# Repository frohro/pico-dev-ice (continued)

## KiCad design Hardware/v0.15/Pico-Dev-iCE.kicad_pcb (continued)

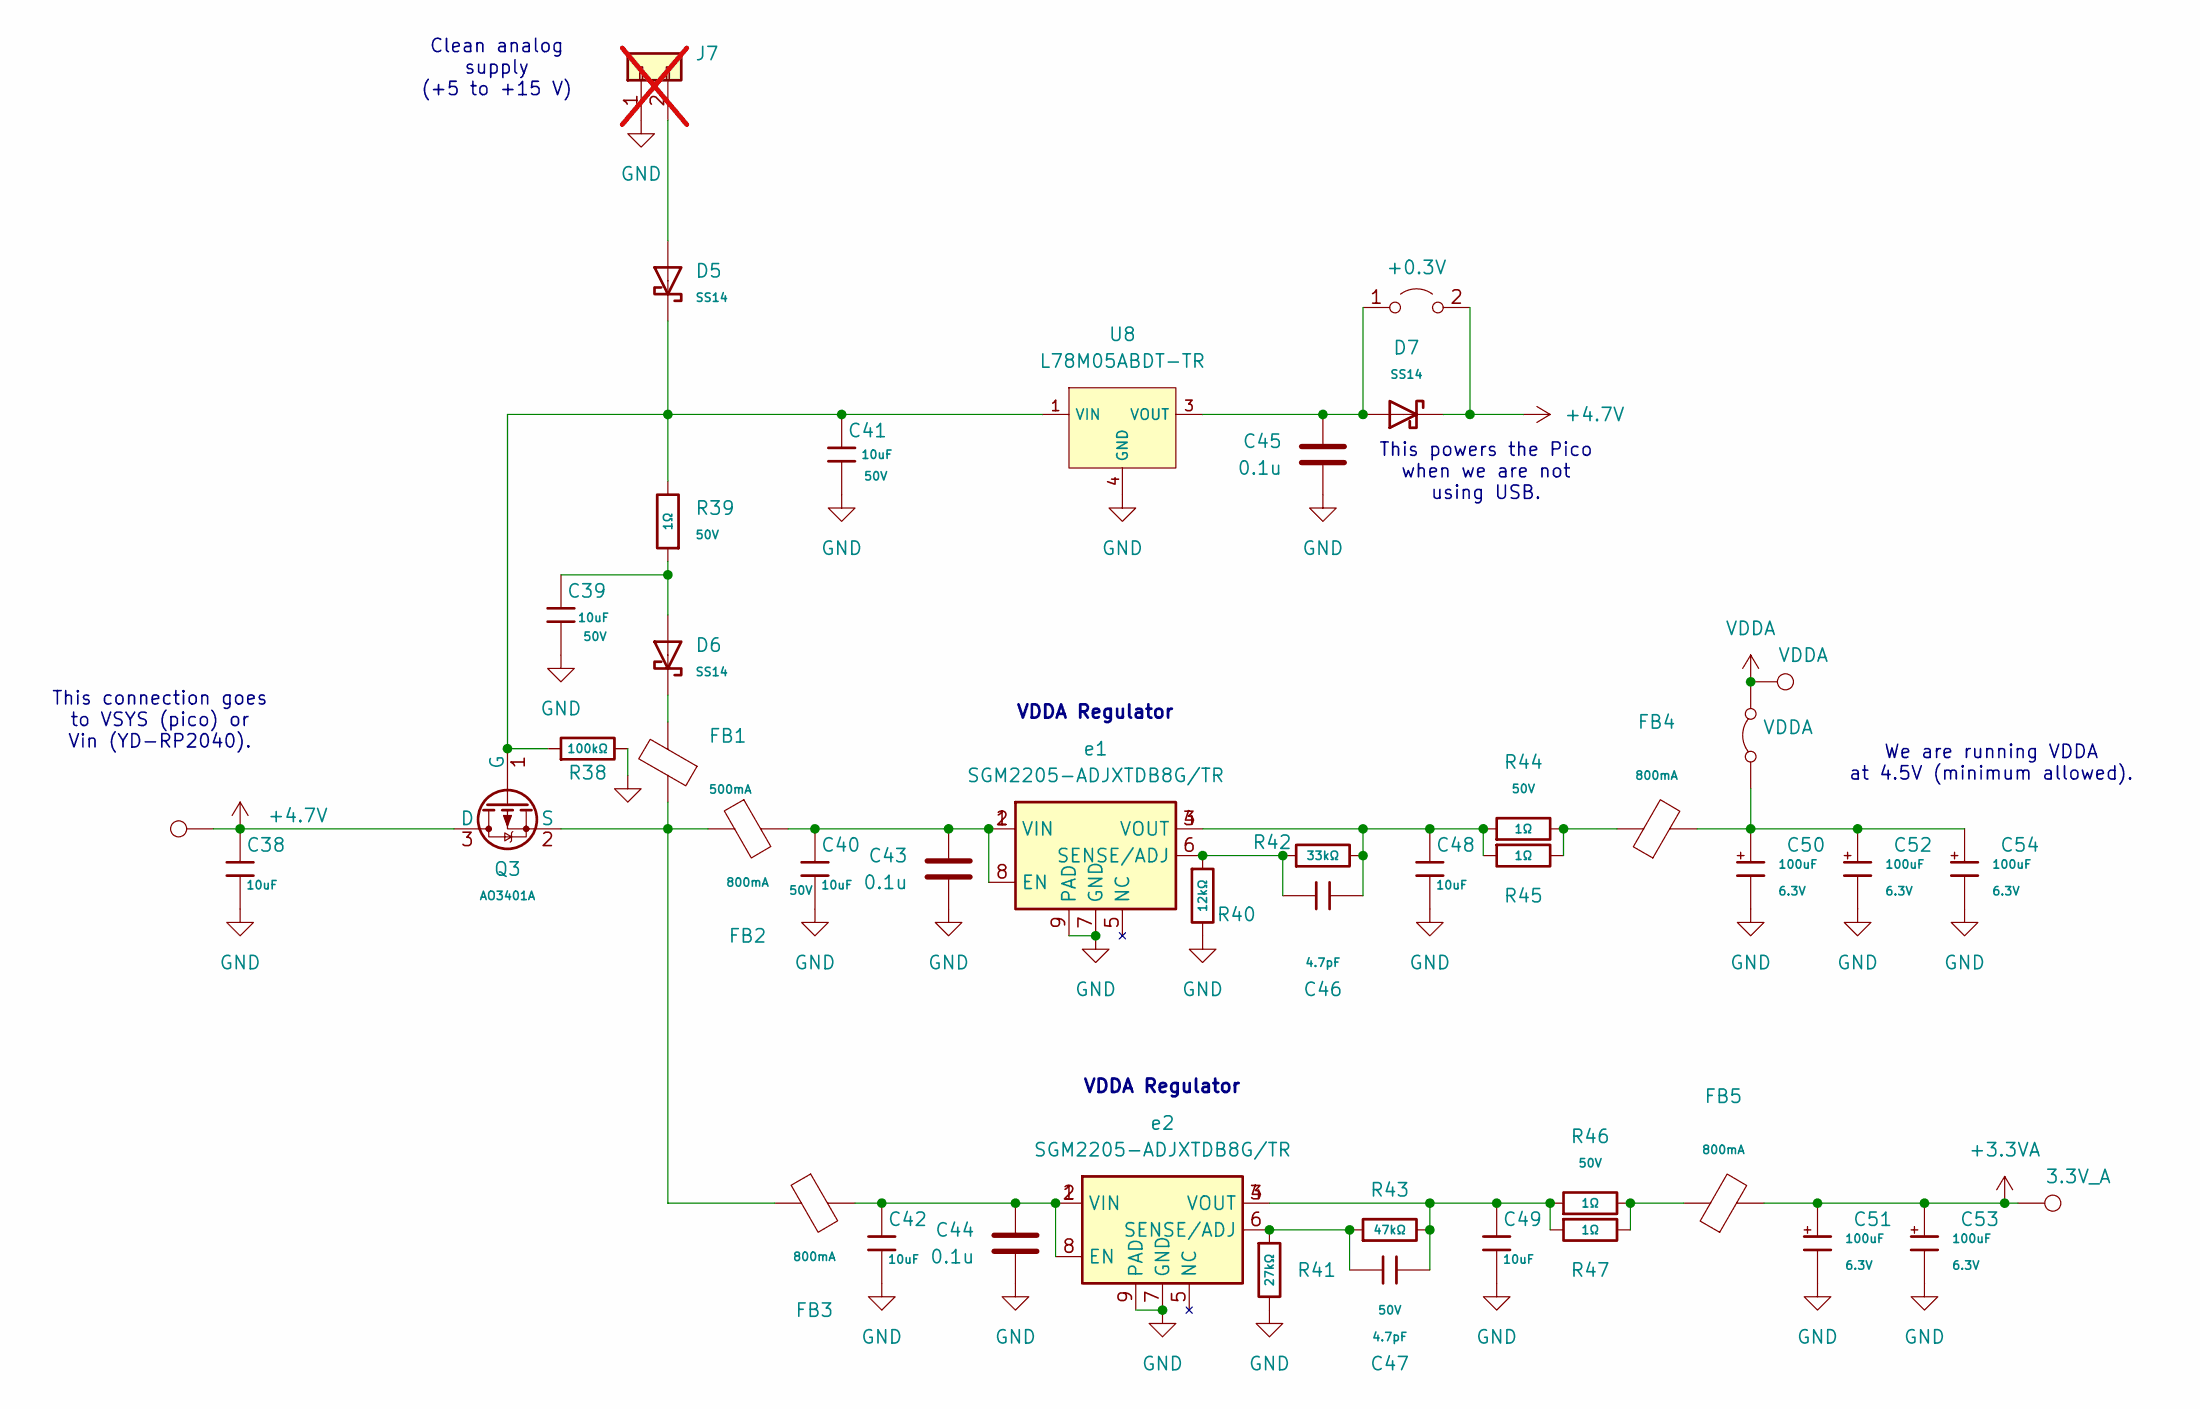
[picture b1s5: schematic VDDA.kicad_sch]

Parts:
C38, C39, C40, C41, C42, C48, C49: 10uF; C_0805; Voltage Rated 50V; Tolerance ±10%; Part GRM21BR61H106KE43L; LCSC C440198
C43, C44, C45: 0.1u; C_0805_2012Metric; LCSC C49678
C46, C47: 4.7pF; C_0603; Voltage Rated 50V; Part 0603CG4R7C500NT; LCSC C1669
C50, C51, C52, C53, C54: 100uF; C_CASE-B-3528-21(mm); Tolerance ±10%; Rated Voltage 6.3V; Part TAJB107K006RNJ; LCSC C16133
D5, D6, D7: SS14; D_SMA; Forward Voltage (Vf@If) 550mV@1A; Reverse Voltage (Vr) 40V; Part SS14; LCSC C2480
FB1: FB_0805; Current Rating 500mA; Tolerance ±25%; Part GZ2012D601TF; LCSC C1017
FB2, FB3, FB4, FB5: FB_0805; Current Rating 800mA; Tolerance ±25%; Part GZ2012D101TF; LCSC C1015
J7: Conn_01x02; PinHeader_1x02_P2.54mm_Vertical; not fitted
JP5: +0.3V; SolderJumper-2_P1.3mm_Open_RoundedPad1.0x1.5mm
JP7: VDDA; SolderJumper-2_P1.3mm_Bridged2Bar_RoundedPad1.0x1.5mm
Q3: AO3401A; Q_SOT-23; Part AO3401A; LCSC C15127
R38: 100kΩ; R_0805; Overload Voltage (Max) 150V; Tolerance ±1%; Part 0805W8F1003T5E; LCSC C149504
R39, R44, R45, R46, R47: 1Ω; R_0402; Overload Voltage (Max) 50V; Tolerance ±1%; Part 0402WGF100KTCE; LCSC C25086
R40: 12kΩ; R_0805; Overload Voltage (Max) 150V; Tolerance ±1%; Part 0805W8F1202T5E; LCSC C17444
R41: 27kΩ; R_0805; Overload Voltage (Max) 150V; Tolerance ±1%; Part 0805W8F2702T5E; LCSC C17593
R42: 33kΩ; R_0805; Overload Voltage (Max) 150V; Tolerance ±1%; Part 0805W8F3302T5E; LCSC C17633
R43: 47kΩ; R_0805; Overload Voltage (Max) 150V; Tolerance ±1%; Part 0805W8F4702T5E; LCSC C17713
TP4: +5; TestPoint_THTPad_D2.5mm_Drill1.2mm
TP5: VDDA; TestPoint_THTPad_D2.5mm_Drill1.2mm
TP6: 3.3V_A; TestPoint_THTPad_D2.5mm_Drill1.2mm
U8: L78M05ABDT-TR; TO-252-2_L6.5-W6.1-P4.58-LS10.0-TL; Output Voltage 5V; Part L78M05ABDT-TR; LCSC C58069
e1, e2: SGM2205-ADJXTDB8G/TR; DFN-8-1EP_3x3mm_P0.65mm_EP1.55x2.4mm; LCSC C5152847

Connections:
+3.3VA: C51.1, C53.1, FB5.2, TP6.1 (1_1); also elsewhere on the board
+4.7V: C38.1, D7.1, JP5.2 (B), Q3.3 (D), TP4.1 (1_1); also elsewhere on the board
GND: C38.2, C39.2, C40.2, C41.2, C42.2, C43.2, C44.2, C45.2, C48.2, C49.2, C50.2, C51.2, C52.2, C53.2, C54.2, J7.1, R38.2, R40.2, R41.2, U8.4 (GND), e1.7 (GND), e1.9 (PAD), e2.7 (GND), e2.9 (PAD); also elsewhere on the board
unnamed: C39.1, D6.2, R39.1
unnamed: C46.1, C48.1, R42.2, R44.1, R45.1, e1.3 (VOUT), e1.4 (VOUT)
unnamed: C47.1, C49.1, R43.2, R46.1, R47.1, e2.3 (VOUT), e2.4 (VOUT)
unnamed: D6.1, FB1.2
unnamed: FB4.1, R44.2, R45.2
unnamed: FB5.1, R46.2, R47.2
unnamed: D5.2, J7.2
unnamed: C45.1, D7.2, JP5.1 (A), U8.3 (VOUT)
unnamed: C50.1, C52.1, C54.1, FB4.2, JP7.1 (A)
unnamed: C41.1, D5.1, Q3.1 (G), R38.1, R39.2, U8.1 (VIN)
unnamed: FB1.1, FB2.1, FB3.1, Q3.2 (S)
unnamed: C40.1, C43.1, FB2.2, e1.1 (VIN), e1.2 (VIN), e1.8 (EN)
unnamed: C46.2, R40.1, R42.1, e1.6 (SENSE/ADJ)
unnamed: C42.1, C44.1, FB3.2, e2.1 (VIN), e2.2 (VIN), e2.8 (EN)
unnamed: C47.2, R41.1, R43.1, e2.6 (SENSE/ADJ)
VDDA: JP7.2 (B), TP5.1 (1_1); also elsewhere on the board

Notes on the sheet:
This connection goes to VSYS (pico) or Vin (YD-RP2040).
VDDA Regulator
We are running VDDA at 4.5V (minimum allowed).
Clean analog supply (+5 to +15 V)
This powers the Pico when we are not using USB.

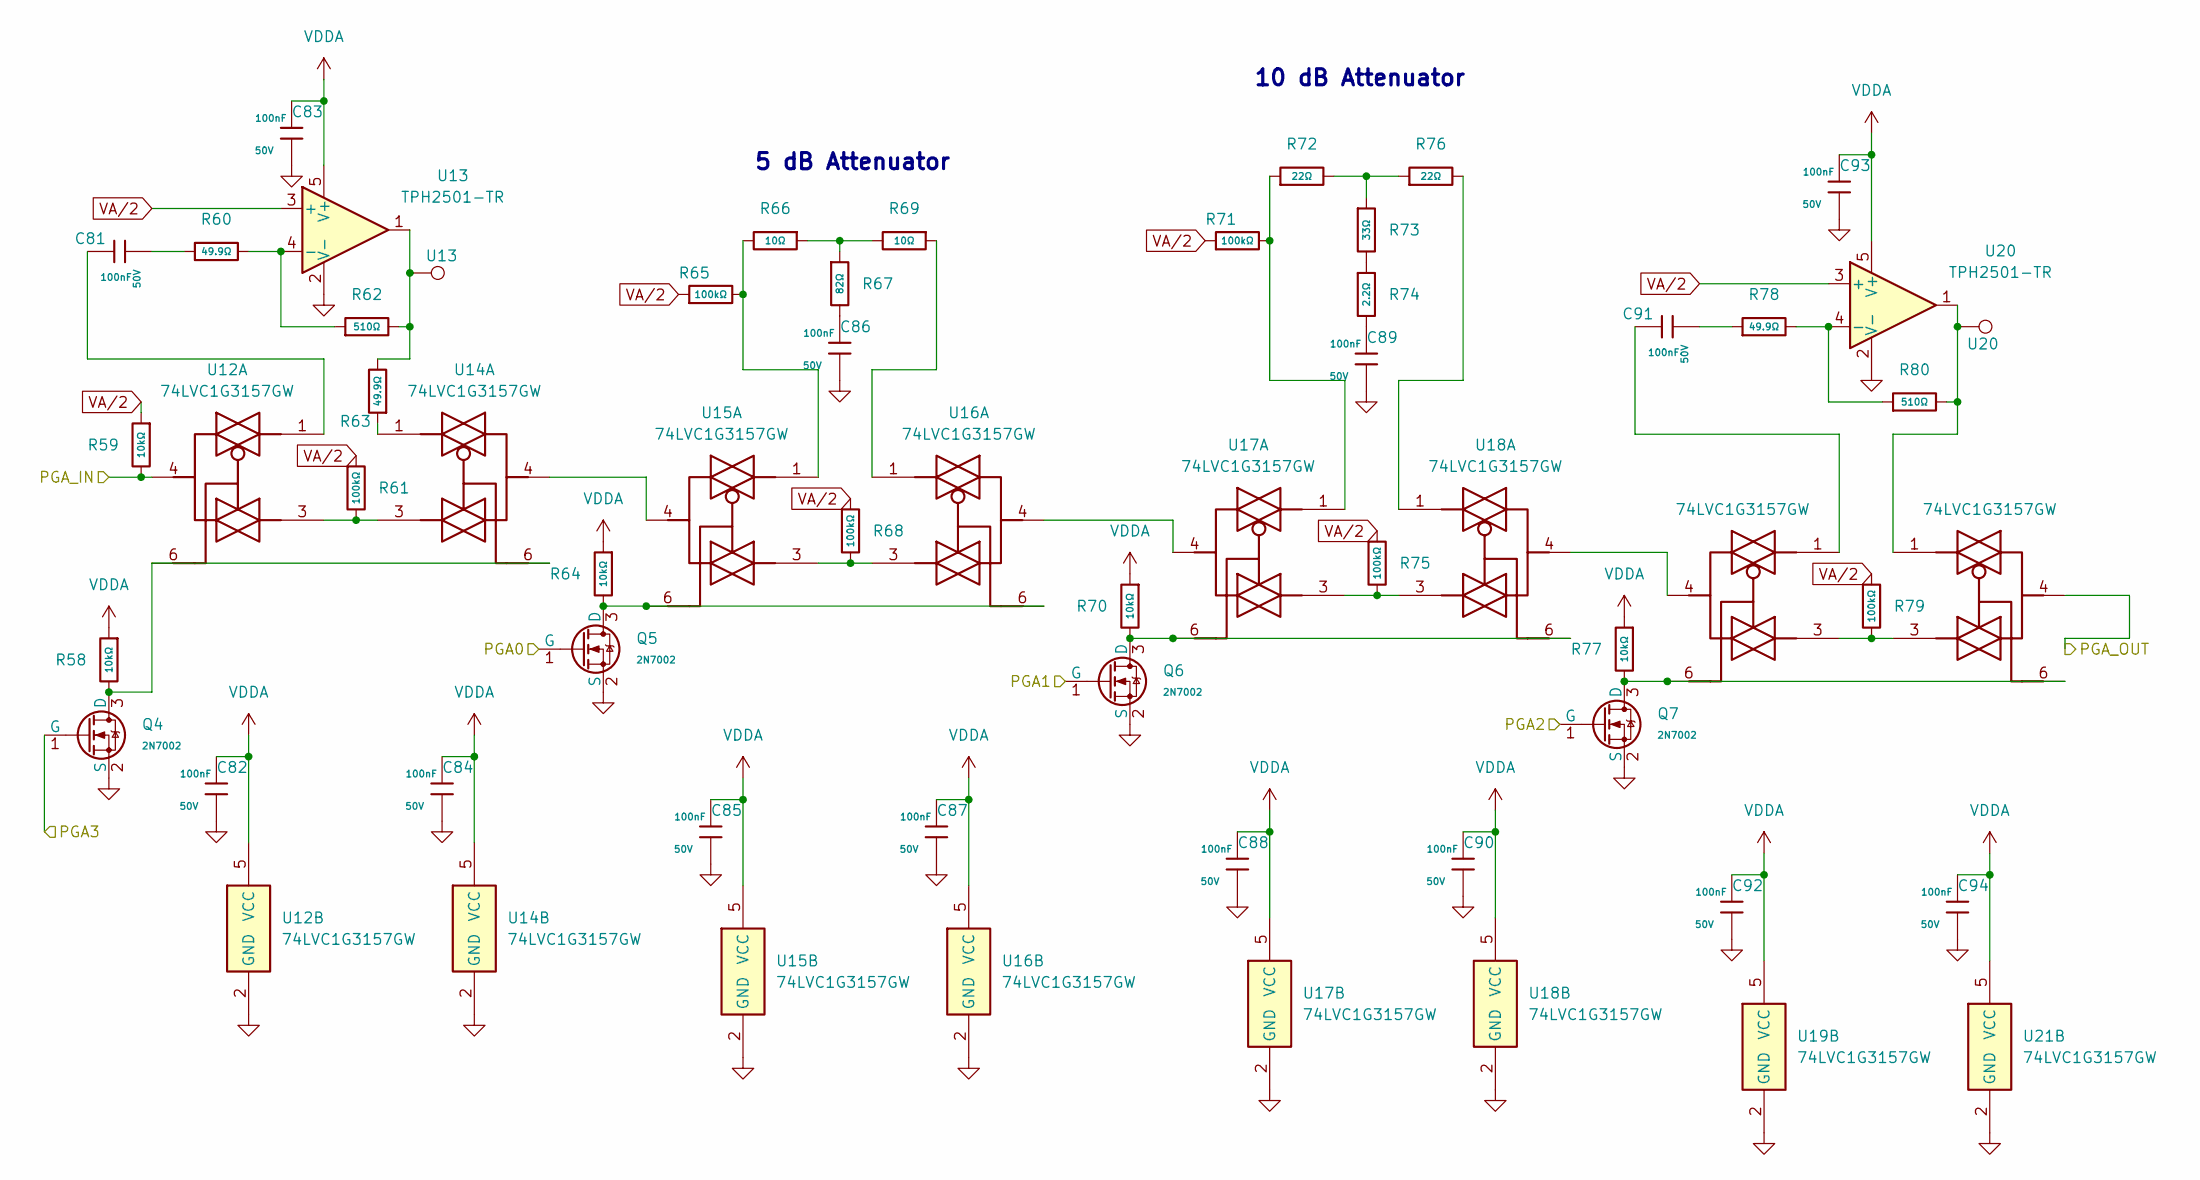
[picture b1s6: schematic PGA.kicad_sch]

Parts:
C81, C82, C83, C84, C85, C86, C87, C88, C89, C90, C91, C92, C93, C94: 100nF; C_0402; Voltage Rated 50V; Tolerance ±10%; Part CL05B104KB54PNC; LCSC C307331
Q4, Q5, Q6, Q7: 2N7002; Q_SOT-23; Part 2N7002K; LCSC C22379475
R58, R59, R64, R70, R77: 10kΩ; R_0402; Overload Voltage (Max) 50V; Tolerance ±1%; Part 0402WGF1002TCE; LCSC C25744
R60, R63, R78: 49.9Ω; R_0402; Overload Voltage (Max) 50V; Tolerance ±1%; Part 0402WGF499JTCE; LCSC C25120
R61, R65, R68, R71, R75, R79: 100kΩ; R_0402; Overload Voltage (Max) 50V; Tolerance ±1%; Part 0402WGF1003TCE; LCSC C25741
R62, R80: 510Ω; R_0402; Overload Voltage (Max) 50V; Tolerance ±1%; Part 0402WGF5100TCE; LCSC C25123
R66, R69: 10Ω; R_0402; Overload Voltage (Max) 50V; Tolerance ±1%; Part 0402WGF100JTCE; LCSC C25077
R67: 82Ω; R_0603; Overload Voltage (Max) 75V; Tolerance ±1%; Part 0603WAF820JT5E; LCSC C23255
R72, R76: 22Ω; R_0603; Overload Voltage (Max) 75V; Tolerance ±1%; Part 0603WAF220JT5E; LCSC C23345
R73: 33Ω; R_0805; Overload Voltage (Max) 150V; Tolerance ±1%; Part 0805W8F330JT5E; LCSC C17634
R74: 2.2Ω; R_0603; Overload Voltage (Max) 75V; Tolerance ±1%; Part 0603WAF220KT5E; LCSC C22939
TP10: U13; TestPoint_THTPad_D2.5mm_Drill1.2mm
TP11: U20; TestPoint_THTPad_D2.5mm_Drill1.2mm
U12, U14, U15, U16, U17, U18, U19, U21: 74LVC1G3157GW; SOT-363_SC-70-6; LCSC C52140494
U13, U20: TPH2501-TR; SOT-23-5; LCSC C126713

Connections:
/Filter Playground/RX_OUT: R59.2, U12.4; also elsewhere on the board
/PGA0: Q5.1 (G); also elsewhere on the board
/PGA1: Q6.1 (G); also elsewhere on the board
/PGA2: Q7.1 (G); also elsewhere on the board
/PGA3: Q4.1 (G); also elsewhere on the board
/RX_OUT: U21.4; also elsewhere on the board
GND: C82.2, C83.2, C84.2, C85.2, C86.2, C87.2, C88.2, C89.2, C90.2, C92.2, C93.2, C94.2, Q4.2 (S), Q5.2 (S), Q6.2 (S), Q7.2 (S), U12.2 (GND), U13.2 (V-), U14.2 (GND), U15.2 (GND), U16.2 (GND), U17.2 (GND), U18.2 (GND), U19.2 (GND), U20.2 (V-), U21.2 (GND); also elsewhere on the board
unnamed: C81.1, U12.1
unnamed: C81.2, R60.1
unnamed: C86.1, R67.2
unnamed: C89.1, R74.2
unnamed: C91.1, U19.1
unnamed: C91.2, R78.1
unnamed: Q4.3 (D), R58.2, U12.6, U14.6
unnamed: Q5.3 (D), R64.2, U15.6, U16.6
unnamed: Q6.3 (D), R70.2, U17.6, U18.6
unnamed: Q7.3 (D), R77.2, U19.6, U21.6
unnamed: R61.2, U12.3, U14.3
unnamed: R62.2, R63.2, TP10.1 (1_1), U13.1
unnamed: R63.1, U14.1
unnamed: R65.2, R66.2, U15.1
unnamed: R66.1, R67.1, R69.2
unnamed: R68.2, U15.3, U16.3
unnamed: R69.1, U16.1
unnamed: R71.2, R72.1, U17.1
unnamed: R72.2, R73.1, R76.1
unnamed: R73.2, R74.1
unnamed: R75.2, U17.3, U18.3
unnamed: R76.2, U18.1
unnamed: R79.2, U19.3, U21.3
unnamed: R80.2, TP11.1 (1_1), U20.1, U21.1
unnamed: R60.2, R62.1, U13.4 (-)
unnamed: U14.4, U15.4
unnamed: U16.4, U17.4
unnamed: U18.4, U19.4
unnamed: R78.2, R80.1, U20.4 (-)
VA/2: R59.1, R61.1, R65.1, R68.1, R71.1, R75.1, R79.1, U13.3 (+), U20.3 (+); also elsewhere on the board
VDDA: C82.1, C83.1, C84.1, C85.1, C87.1, C88.1, C90.1, C92.1, C93.1, C94.1, R58.1, R64.1, R70.1, R77.1, U12.5 (VCC), U13.5 (V+), U14.5 (VCC), U15.5 (VCC), U16.5 (VCC), U17.5 (VCC), U18.5 (VCC), U19.5 (VCC), U20.5 (V+), U21.5 (VCC); also elsewhere on the board

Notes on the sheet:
5 dB Attenuator
10 dB Attenuator

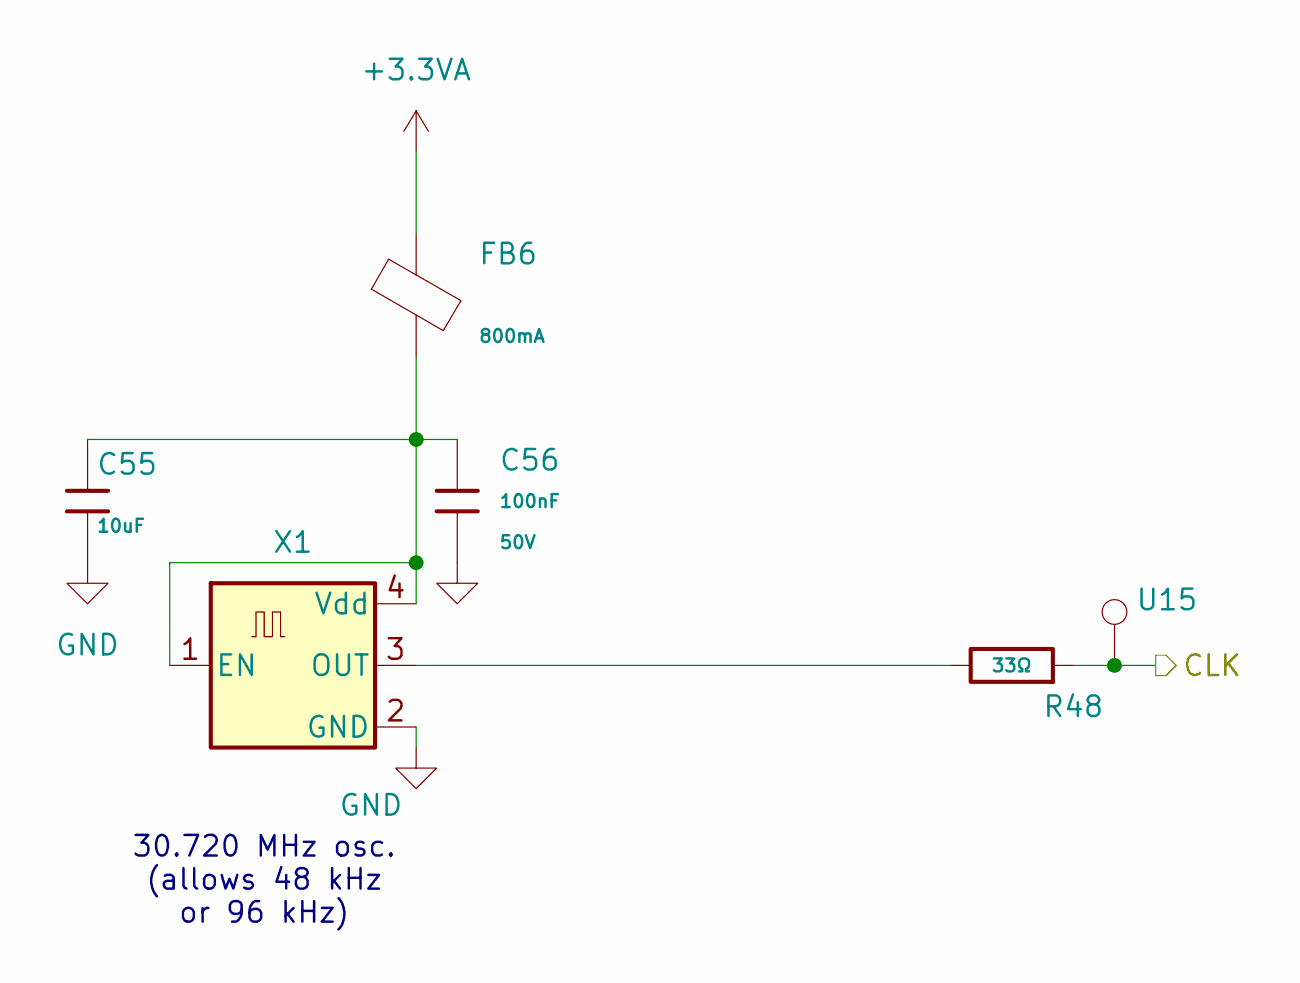
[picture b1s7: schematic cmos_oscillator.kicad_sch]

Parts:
C55: 10uF; C_0805; Voltage Rated 50V; Tolerance ±10%; Part GRM21BR61H106KE43L; LCSC C440198
C56: 100nF; C_0402; Voltage Rated 50V; Tolerance ±10%; Part CL05B104KB54PNC; LCSC C307331
FB6: FB_0805; Current Rating 800mA; Tolerance ±25%; Part GZ2012D101TF; LCSC C1015
R48: 33Ω; R_0805; Overload Voltage (Max) 150V; Tolerance ±1%; Part 0805W8F330JT5E; LCSC C17634
TP16: U15; TestPoint_THTPad_D2.5mm_Drill1.2mm
X1: SG-8018CE 30.720000MHz TJHPA; Oscillator_SMD_Abracon_ASE-4Pin_3.2x2.5mm; LCSC C390505

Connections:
+3.3VA: FB6.1; also elsewhere on the board
/CLK: R48.1, TP16.1 (1_1); also elsewhere on the board
GND: C55.2, C56.2, X1.2 (GND); also elsewhere on the board
unnamed: C55.1, C56.1, FB6.2, X1.1 (EN), X1.4 (Vdd)
unnamed: R48.2, X1.3 (OUT)

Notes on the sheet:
30.720 MHz osc. (allows 48 kHz or 96 kHz)

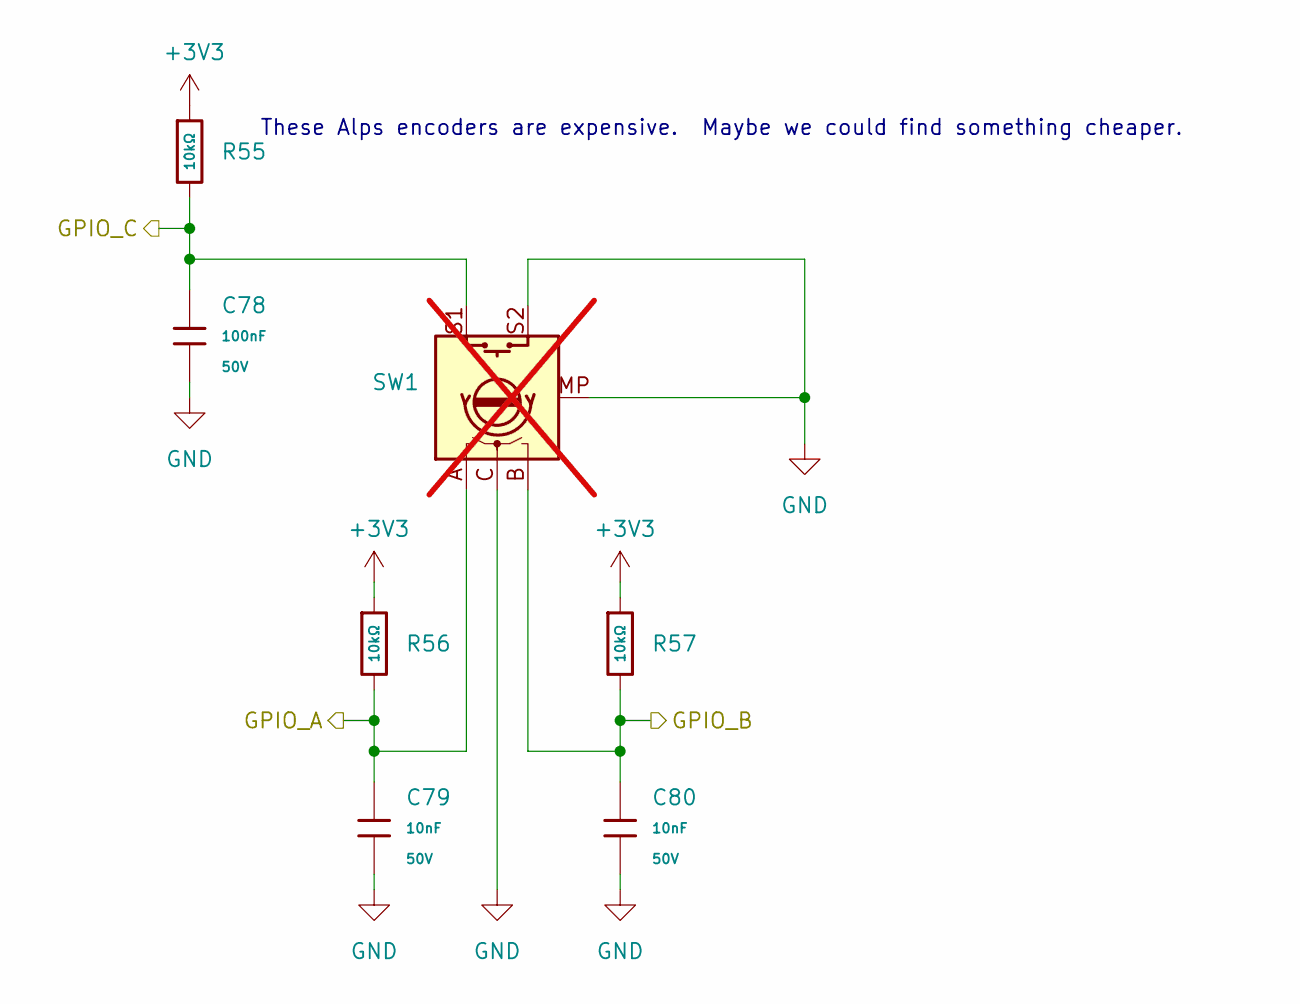
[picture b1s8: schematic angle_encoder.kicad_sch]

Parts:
C78: 100nF; C_0402; Voltage Rated 50V; Tolerance ±10%; Part CL05B104KB54PNC; LCSC C307331
C79, C80: 10nF; C_0402; Voltage Rated 50V; Tolerance ±10%; Part CL05B103KB5NNNC; LCSC C15195
R55, R56, R57: 10kΩ; R_0402; Overload Voltage (Max) 50V; Tolerance ±1%; Part 0402WGF1002TCE; LCSC C25744
SW1: RotaryEncoder_Switch_MP; RotaryEncoder_Alps_EC11E-Switch_Vertical_H20mm; LCSC C202365; not fitted

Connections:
+3V3: R55.1, R56.1, R57.1; also elsewhere on the board
/ANG_0: C79.1, R56.2, SW1.A; also elsewhere on the board
/ANG_1: C80.1, R57.2, SW1.B; also elsewhere on the board
/ANG_2: C78.1, R55.2, SW1.S1; also elsewhere on the board
GND: C78.2, C79.2, C80.2, SW1.C, SW1.MP, SW1.S2; also elsewhere on the board

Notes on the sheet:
These Alps encoders are expensive. Maybe we could find something cheaper.

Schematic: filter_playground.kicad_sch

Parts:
C95, C96, C97, C98, C99, C100, C101, C102, C103, C104, C105: 100nF; C_0402; Voltage Rated 50V; Tolerance ±10%; Part CL05B104KB54PNC; LCSC C307331
J10: SDR ANT; Conn_Coaxial_Frohne; not fitted
Je5, Je6: Filter; PinHeader_1x04_P2.54mm_Vertical; LCSC C2718488
Q8, Q9: 2N7002; Q_SOT-23; Part 2N7002K; LCSC C22379475
R81, R84, R87, R88: 10kΩ; R_0402; Overload Voltage (Max) 50V; Tolerance ±1%; Part 0402WGF1002TCE; LCSC C25744
R82, R83, R85, R86: 100kΩ; R_0402; Overload Voltage (Max) 50V; Tolerance ±1%; Part 0402WGF1003TCE; LCSC C25741
TP12, TP13, TP17, TP18: GND; TestPoint_THTPad_D2.5mm_Drill1.2mm
TR4: H1102NLT; Transformer_Ethernet_Wuerth_749013011A; LCSC C20623173
U22, U23, U24: 74LVC1G3157GW; SOT-363_SC-70-6; LCSC C52140494

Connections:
/BAND_SW: Q8.1 (G); also elsewhere on the board
/Filter Playground/RX_OUT: C104.2; also elsewhere on the board
/TX_SDR: C105.2; also elsewhere on the board
/~T/R: Q9.1 (G); also elsewhere on the board
GND: C97.2, C100.2, C103.2, Je5.2, Je5.3, Je6.2, Je6.3, Q8.2 (S), Q9.2 (S), TP12.1 (1_1), TP13.1 (1_1), TP17.1 (1_1), TP18.1 (1_1), TR4.6 (RD+), U22.2 (GND), U23.2 (GND), U24.2 (GND); also elsewhere on the board
unnamed: C96.2, R81.2, U22.4
unnamed: C98.1, R82.2, U22.1
unnamed: C99.1, R83.2, U22.3
unnamed: C101.2, R85.2, U23.1
unnamed: C102.2, R86.2, U23.3
unnamed: C104.1, U24.3
unnamed: C105.1, U24.1
unnamed: J10.2 (Ext), TR4.11 (RX+)
unnamed: C95.1, J10.1 (In)
unnamed: C98.2, Je5.1
unnamed: C101.1, Je5.4
unnamed: C99.2, Je6.1
unnamed: C102.1, Je6.4
unnamed: Q8.3 (D), R84.2, U22.6, U23.6
unnamed: Q9.3 (D), R88.2, U24.6
unnamed: R87.2, U23.4, U24.4
unnamed: C96.1, TR4.8 (RD-)
unnamed: C95.2, TR4.9 (RX-)
VA/2: R81.1, R82.1, R83.1, R85.1, R86.1, R87.1; also elsewhere on the board
VDDA: C97.1, C100.1, C103.1, R84.1, R88.1, U22.5 (VCC), U23.5 (VCC), U24.5 (VCC); also elsewhere on the board

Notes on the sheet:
Filters
T/R Switch
Scope GND connections

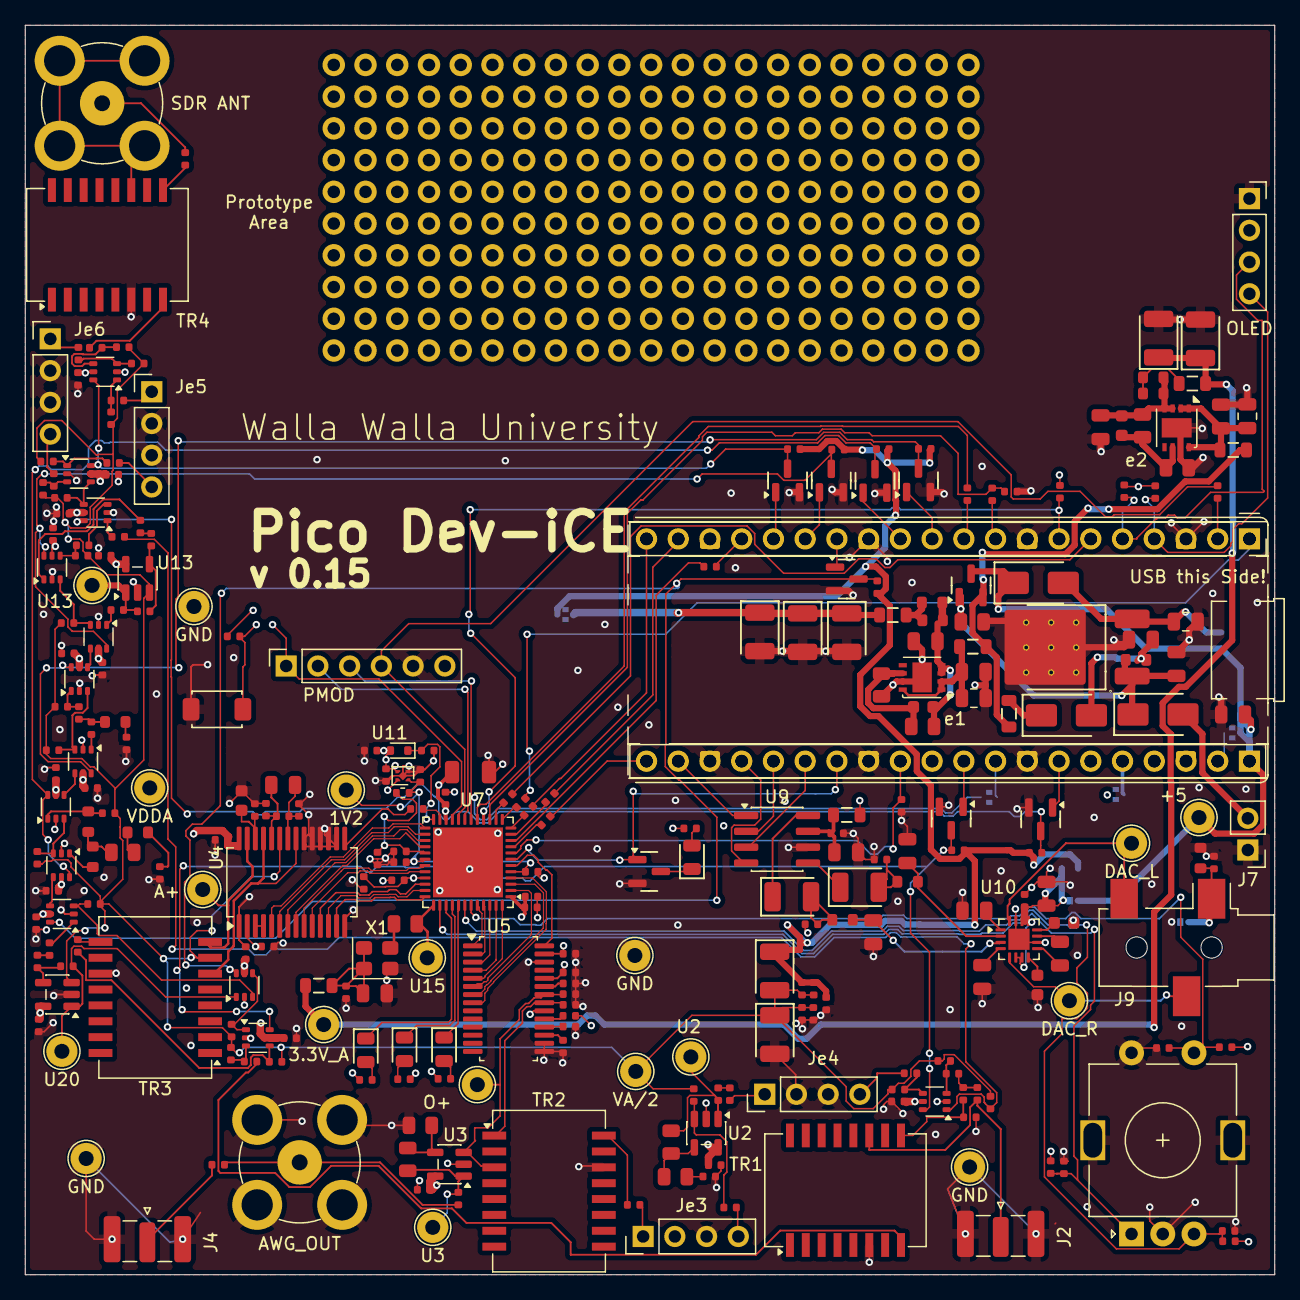
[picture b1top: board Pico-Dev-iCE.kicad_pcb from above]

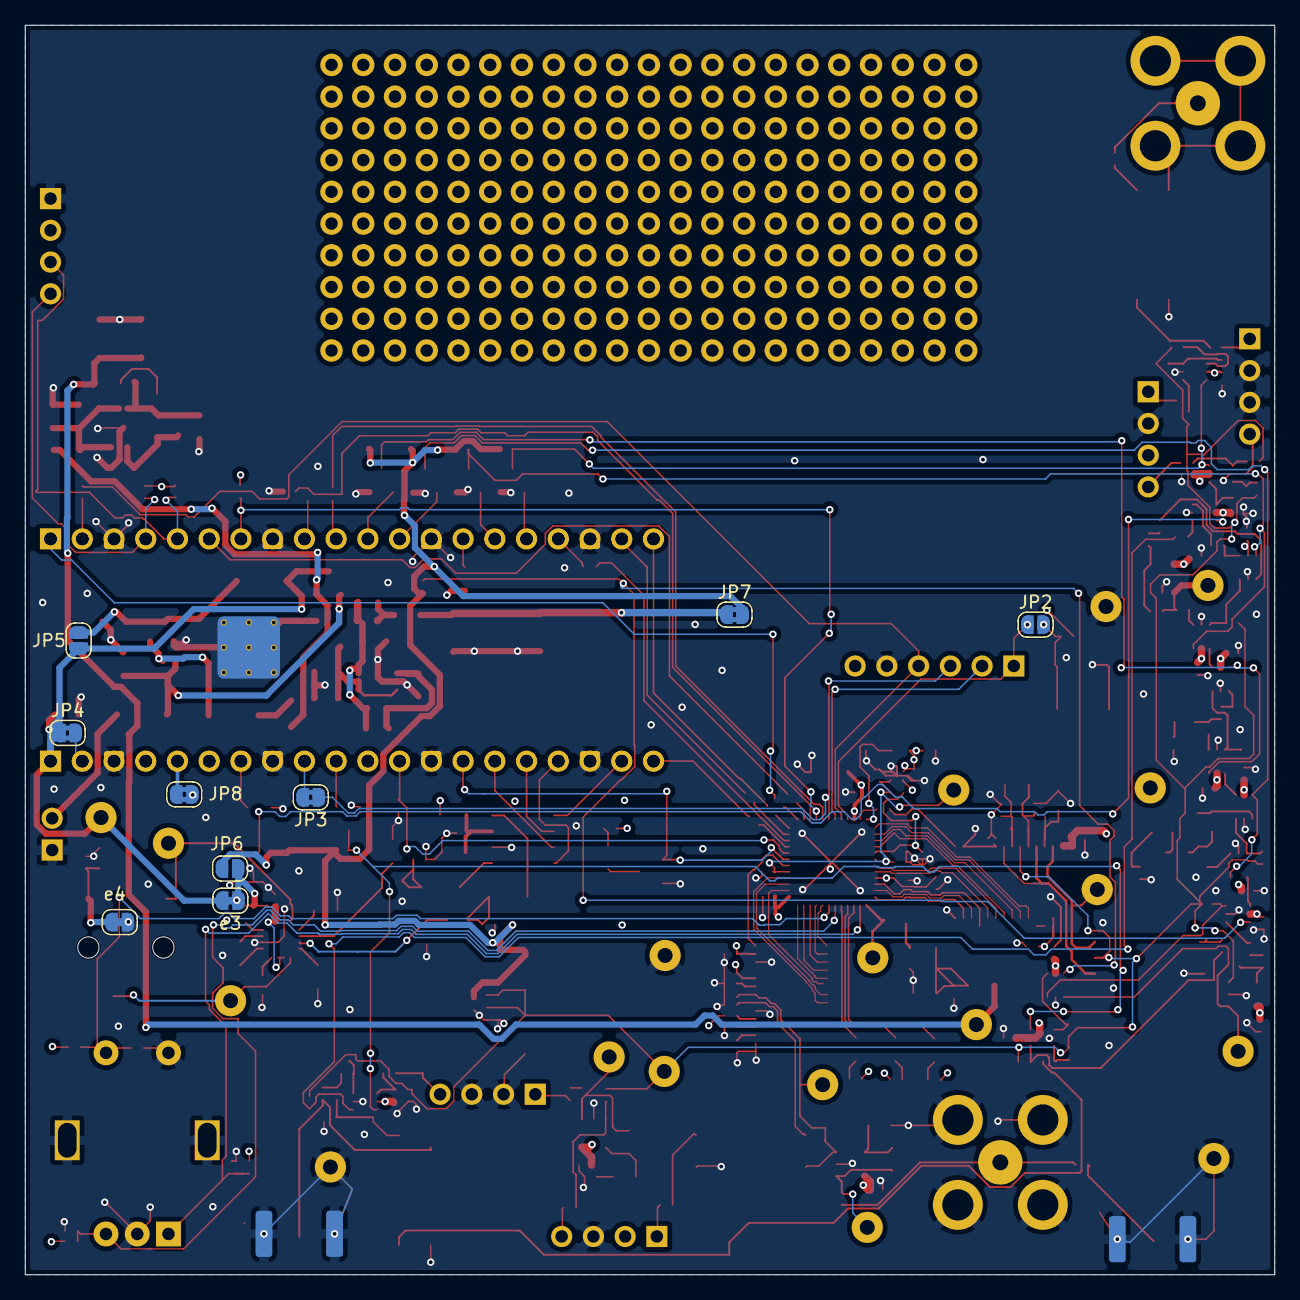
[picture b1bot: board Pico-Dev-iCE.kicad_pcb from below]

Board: 4 copper layers, 100.0 x 100.0 mm, 299 parts (9 on the bottom side), 204 nets.

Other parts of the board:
J8: OLED; PinSocket_1x04_P2.54mm_Vertical

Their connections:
+3V3: J8.2; also elsewhere on the board
/SCL: J8.3; also elsewhere on the board
/SDA: J8.4; also elsewhere on the board
GND: J8.1; also elsewhere on the board

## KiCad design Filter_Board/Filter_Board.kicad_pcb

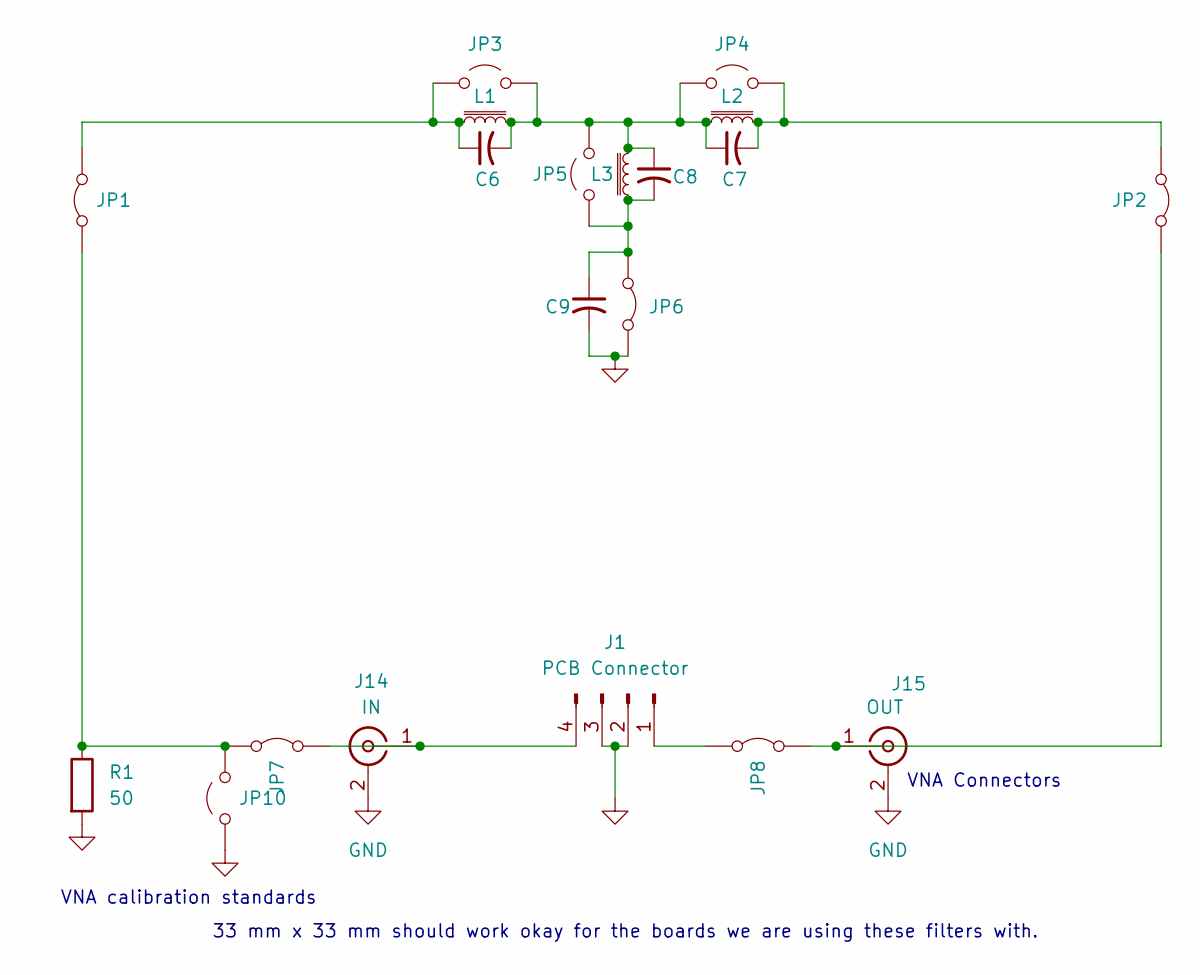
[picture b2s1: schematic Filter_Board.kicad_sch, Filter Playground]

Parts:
C6, C7, C8, C9: C_Small_US; Capacitor_multi_no_trimmer
J1: PCB Connector; PinHeader_1x04_P2.54mm_Horizontal
J14: IN; SMA_Amphenol_132289_EdgeMount
J15: OUT; SMA_Amphenol_132289_EdgeMount
JP1, JP2, JP6, JP7, JP8: Jumper_2_Bridged; SolderJumper-2_P1.3mm_Bridged_RoundedPad1.0x1.5mm
JP3, JP4, JP5, JP10: Jumper_2_Open; SolderJumper-2_P1.3mm_Open_RoundedPad1.0x1.5mm
L1, L2, L3: L_Iron_Small; Inductor_Multi
R1: 50; C_0805_2012Metric_Pad1.18x1.45mm_HandSolder

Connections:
GND: C9.2, J1.2, J1.3, J14.2 (Ext), J15.2 (Ext), JP6.1 (A), JP10.1 (A), R1.2
unnamed: J1.1, JP8.2 (B)
unnamed: J1.4, J14.1 (In), JP7.1 (A)
unnamed: J15.1 (In), JP2.1 (A), JP8.1 (A)
unnamed: JP1.1 (A), JP7.2 (B), JP10.2 (B), R1.1
unnamed: C6.1, JP1.2 (B), JP3.1 (A), L1.1
unnamed: C7.2, JP2.2 (B), JP4.2 (B), L2.2
unnamed: C6.2, C7.1, C8.1, JP3.2 (B), JP4.1 (A), JP5.1 (A), L1.2, L2.1, L3.1
unnamed: C8.2, C9.1, JP5.2 (B), JP6.2 (B), L3.2

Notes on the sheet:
VNA Connectors
33 mm x 33 mm should work okay for the boards we are using these filters with.
VNA calibration standards

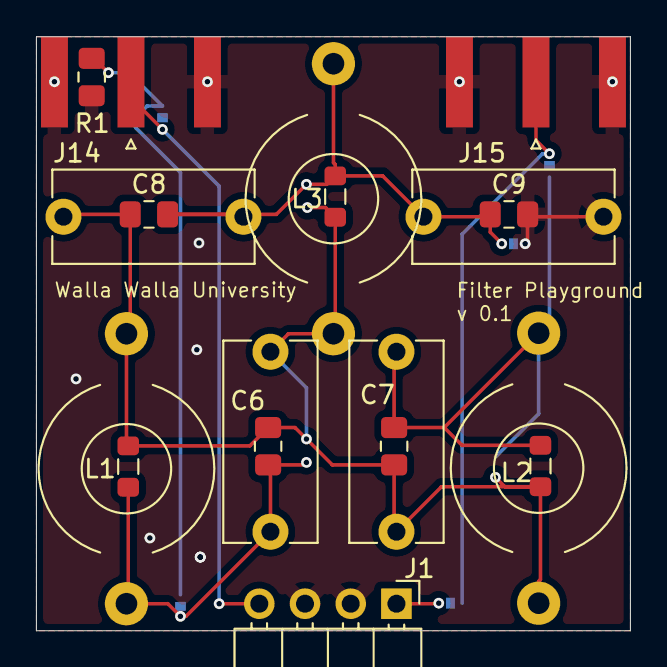
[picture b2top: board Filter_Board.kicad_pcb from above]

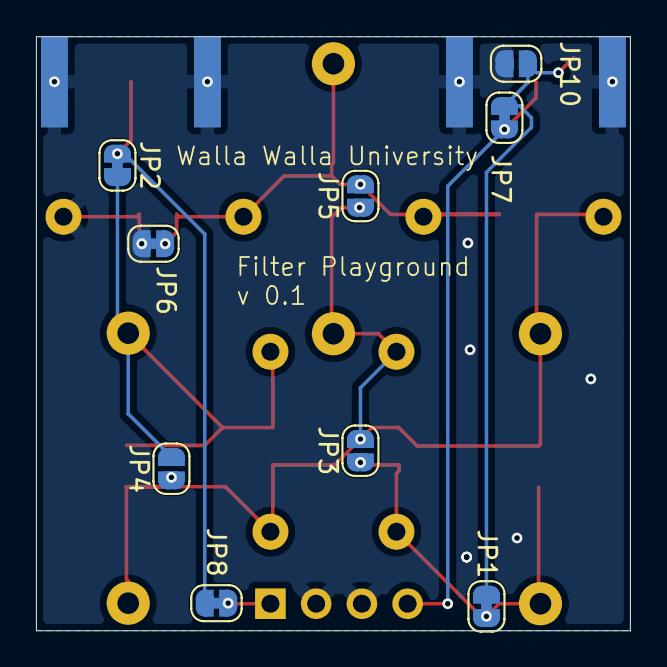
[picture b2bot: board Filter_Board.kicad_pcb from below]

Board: 2 copper layers, 33.0 x 33.0 mm, 20 parts (9 on the bottom side), 9 nets.

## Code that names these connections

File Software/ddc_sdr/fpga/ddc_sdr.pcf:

# Dev-iCE iCE40UP5K-SG48 constraints for the DDC SDR top level.
#
# These names are the Pico-side contract documented in README.md. Keep the
# top-level port names stable so the bitstream can be built independently of
# the RP2040 firmware.

set_io clk 37
set_io adc_clk 23
set_io dac_clk 6

set_io adc_data[0] 25
set_io adc_data[1] 26
set_io adc_data[2] 27
set_io adc_data[3] 28
set_io adc_data[4] 31
set_io adc_data[5] 32
set_io adc_data[6] 34
set_io adc_data[7] 35
set_io adc_otr 36

set_io dac_data[0] 4
set_io dac_data[1] 3
set_io dac_data[2] 2
set_io dac_data[3] 48
set_io dac_data[4] 47
set_io dac_data[5] 46
set_io dac_data[6] 45
set_io dac_data[7] 44

set_io spi_miso 14
set_io spi_mosi 17
set_io spi_sck 15
set_io spi_cs 16

set_io i2s_bck 11
set_io i2s_ws 12
set_io i2s_rx_data 10
set_io i2s_tx_data 9
set_io fpga_int 13

set_io encoder_a 38
set_io encoder_b 42
set_io encoder_button 43

set_io pmod[0] 21
set_io pmod[1] 19
set_io pmod[2] 18
set_io pmod[3] 20

set_io led_red 39
set_io led_yellow 40
set_io led_green 41
set_io cdone 7
set_io creset 8
